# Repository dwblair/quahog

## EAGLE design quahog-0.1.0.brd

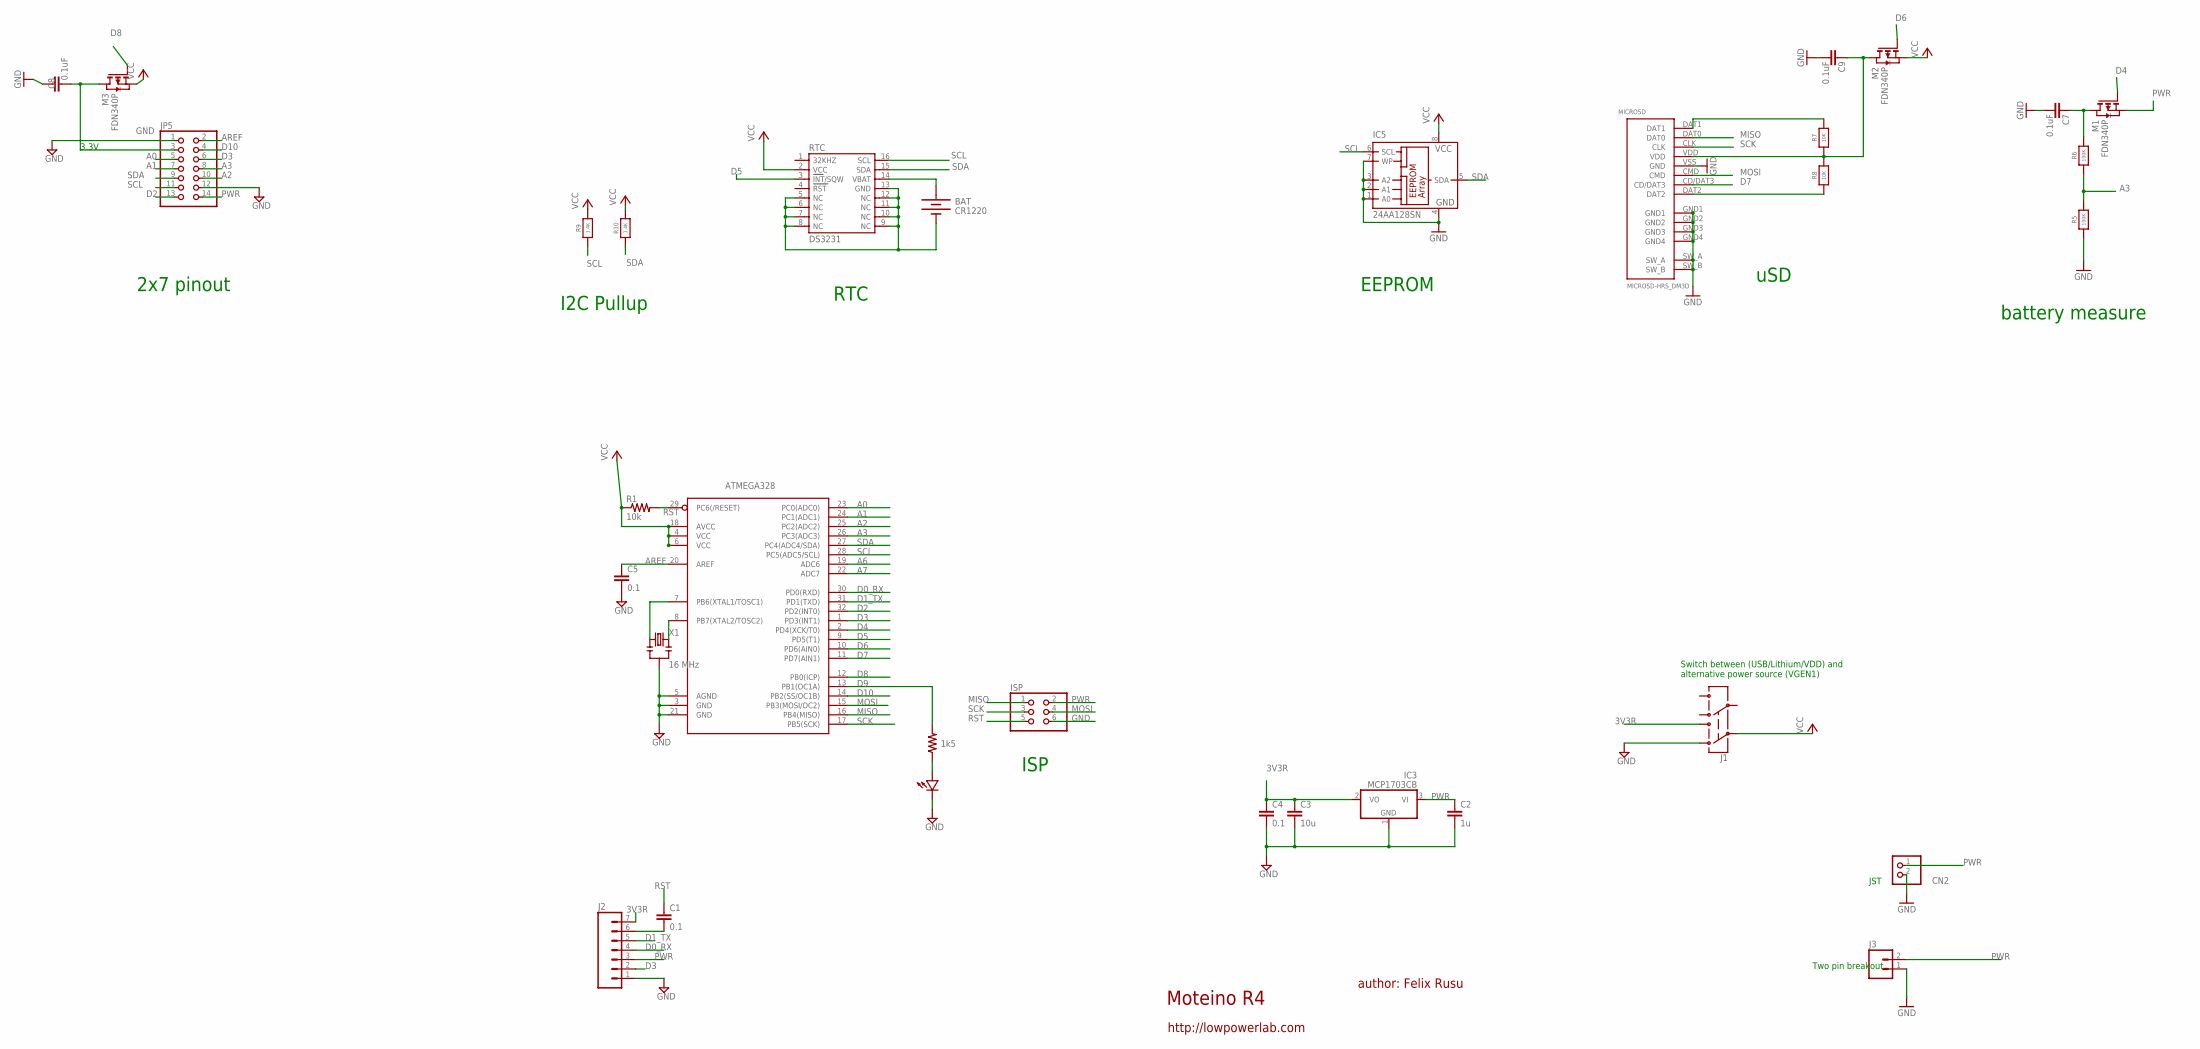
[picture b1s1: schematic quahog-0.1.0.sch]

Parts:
ATMEGA328: ATMega-328; TQFP32-08
BAT: CR1220; BATTCON_12MM_SMT
C1, C4, C5: 0.1; 0603-CAP
C2: 1u; 0603-CAP
C3: 10u; 0805-CAP
C7, C8, C9: 0.1uF; 0603-CAP
CN2: JST_2PIN-SMT-RA; JST-PH-2-SMT-RA
D1: LED0603; 0603-LED
IC3: MCP1703CB; SOT23
IC5: 24AA128SN; SO-08
ISP: PINHD-2X3; 2X03
J1: AYZ0202
J2: M07; 1X07
J3: M02PTH; 1X02
JP5: PINHD-2X7; 2X07
M1, M2, M3: FDN340P; SOT-23
MICROSD: MICROSD-HRS_DM3D; DM3D
R1: 10k; 0603-RES
R2: 1k5; 0603-RES
R5, R6: 100K; 0603-NO
R7, R8: 10K; 0603-NO
R9, R10: 1.4K; 0603-NO
RTC: DS3231
X1: 16 MHz; RESONATOR-SMD

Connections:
3V3R: C3.1, C4.1, IC3.2 (VO), J1.1 (3), J2.7
A0: ATMEGA328.23 (PC0(ADC0)), JP5.5
A1: ATMEGA328.24 (PC1(ADC1)), JP5.7
A2: ATMEGA328.25 (PC2(ADC2)), JP5.10
A3: ATMEGA328.26 (PC3(ADC3)), JP5.8, R5.2, R6.1
A6: ATMEGA328.19 (ADC6)
A7: ATMEGA328.22 (ADC7)
AREF: ATMEGA328.20 (AREF), C5.1, JP5.2
D0_RX: ATMEGA328.30 (PD0(RXD)), J2.4
D1_TX: ATMEGA328.31 (PD1(TXD)), J2.5
D2: ATMEGA328.32 (PD2(INT0)), JP5.13
D3: ATMEGA328.1 (PD3(INT1)), J2.2, JP5.6
D4: ATMEGA328.2 (PD4(XCK/T0)), M1.3 (G)
D5: ATMEGA328.9 (PD5(T1)), RTC.3 (INT/SQW)
D6: ATMEGA328.10 (PD6(AIN0)), M2.3 (G)
D7: ATMEGA328.11 (PD7(AIN1)), MICROSD.CD/DAT3
D8: ATMEGA328.12 (PB0(ICP)), M3.3 (G)
D9: ATMEGA328.13 (PB1(OC1A)), R2.2
D10: ATMEGA328.14 (PB2(SS/OC1B)), JP5.4
GND: ATMEGA328.3 (GND), ATMEGA328.5 (AGND), ATMEGA328.21 (GND), BAT.P$1 (-), C2.2, C3.2, C4.2, C5.2, C7.1, C8.2, C9.1, CN2.2 (1), D1.MINUS, IC3.1 (GND), IC5.1 (A0), IC5.2 (A1), IC5.3 (A2), IC5.4 (GND), IC5.7 (WP), ISP.6, J1.3 (1), J2.1, J3.1, JP5.1, JP5.12, MICROSD.GND1, MICROSD.GND2, MICROSD.GND3, MICROSD.GND4, MICROSD.SW_A, MICROSD.SW_B, MICROSD.VSS (GND), R5.1, RTC.5 (NC), RTC.6 (NC), RTC.7 (NC), RTC.8 (NC), RTC.9 (NC), RTC.10 (NC), RTC.11 (NC), RTC.12 (NC), RTC.13 (GND), X1.2
MISO: ATMEGA328.16 (PB4(MISO)), ISP.1, MICROSD.DAT0
MOSI: ATMEGA328.15 (PB3(MOSI/OC2)), ISP.4, MICROSD.CMD
unnamed: ATMEGA328.7 (PB6(XTAL1/TOSC1)), X1.1
unnamed: D1.PLUS, R2.1
unnamed: C9.2, M2.1 (D), MICROSD.VDD, R7.1, R8.2
unnamed: C8.1, JP5.3, M3.1 (D)
unnamed: C7.2, M1.1 (D), R6.2
unnamed: MICROSD.DAT1, R7.2
unnamed: MICROSD.DAT2, R8.1
unnamed: C1.2, J2.6
unnamed: ATMEGA328.8 (PB7(XTAL2/TOSC2)), X1.3
PWR: C2.1, CN2.1 (2), IC3.3 (VI), ISP.2, J2.3, J3.2, JP5.14, M1.2 (S)
RST: ATMEGA328.29 (PC6(/RESET)), C1.1, ISP.5, R1.2
RTC_BATT: BAT.P$2 (+), RTC.14 (VBAT)
SCK: ATMEGA328.17 (PB5(SCK)), ISP.3, MICROSD.CLK
SCL: ATMEGA328.28 (PC5(ADC5/SCL)), IC5.6 (SCL), JP5.11, R9.1, RTC.16 (SCL)
SDA: ATMEGA328.27 (PC4(ADC4/SDA)), IC5.5 (SDA), JP5.9, R10.1, RTC.15 (SDA)
VCC: ATMEGA328.4 (VCC), ATMEGA328.6 (VCC), ATMEGA328.18 (AVCC), IC5.8 (VCC), J1.2, M2.2 (S), M3.2 (S), R1.1, R9.2, R10.2, RTC.2 (VCC)

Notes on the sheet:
Moteino R4
author: Felix Rusu
http://lowpowerlab.com
3.3V
RTC
uSD
2x7 pinout
I2C Pullup
ISP
EEPROM
battery measure
Switch between (USB/Lithium/VDD) and alternative power source (VGEN1)
Two pin breakout
JST

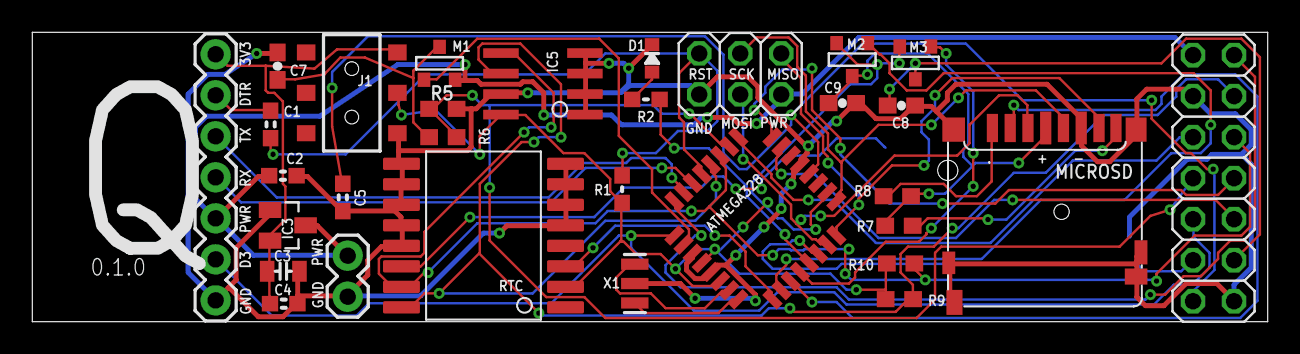
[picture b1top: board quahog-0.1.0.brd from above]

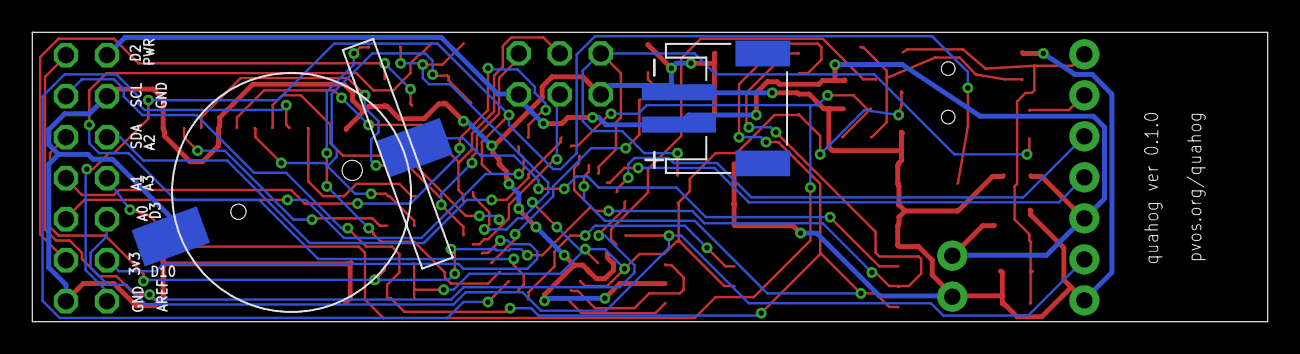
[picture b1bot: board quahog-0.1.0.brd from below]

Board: 2 copper layers, 76.5 x 17.9 mm, 33 parts (2 on the bottom side), 36 nets.

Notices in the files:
parts and their libraries:
SparkFun-Connectors: Licensing: CC v3.0 Share-Alike You are welcome to use this library for commercial purposes.
microbuilder: This work is placed in the public domain, and may be freely used for commercial and non-commercial work with the following conditions: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
